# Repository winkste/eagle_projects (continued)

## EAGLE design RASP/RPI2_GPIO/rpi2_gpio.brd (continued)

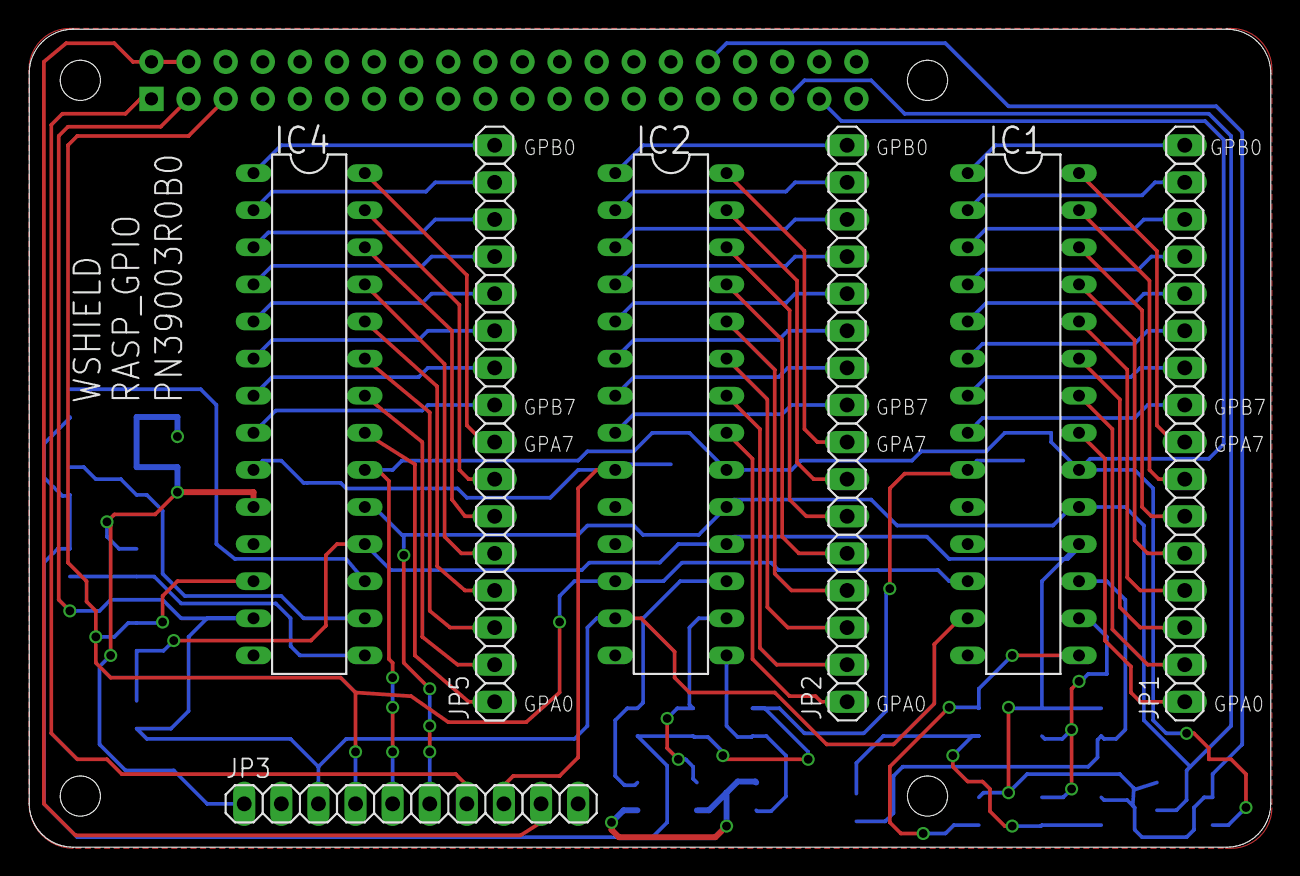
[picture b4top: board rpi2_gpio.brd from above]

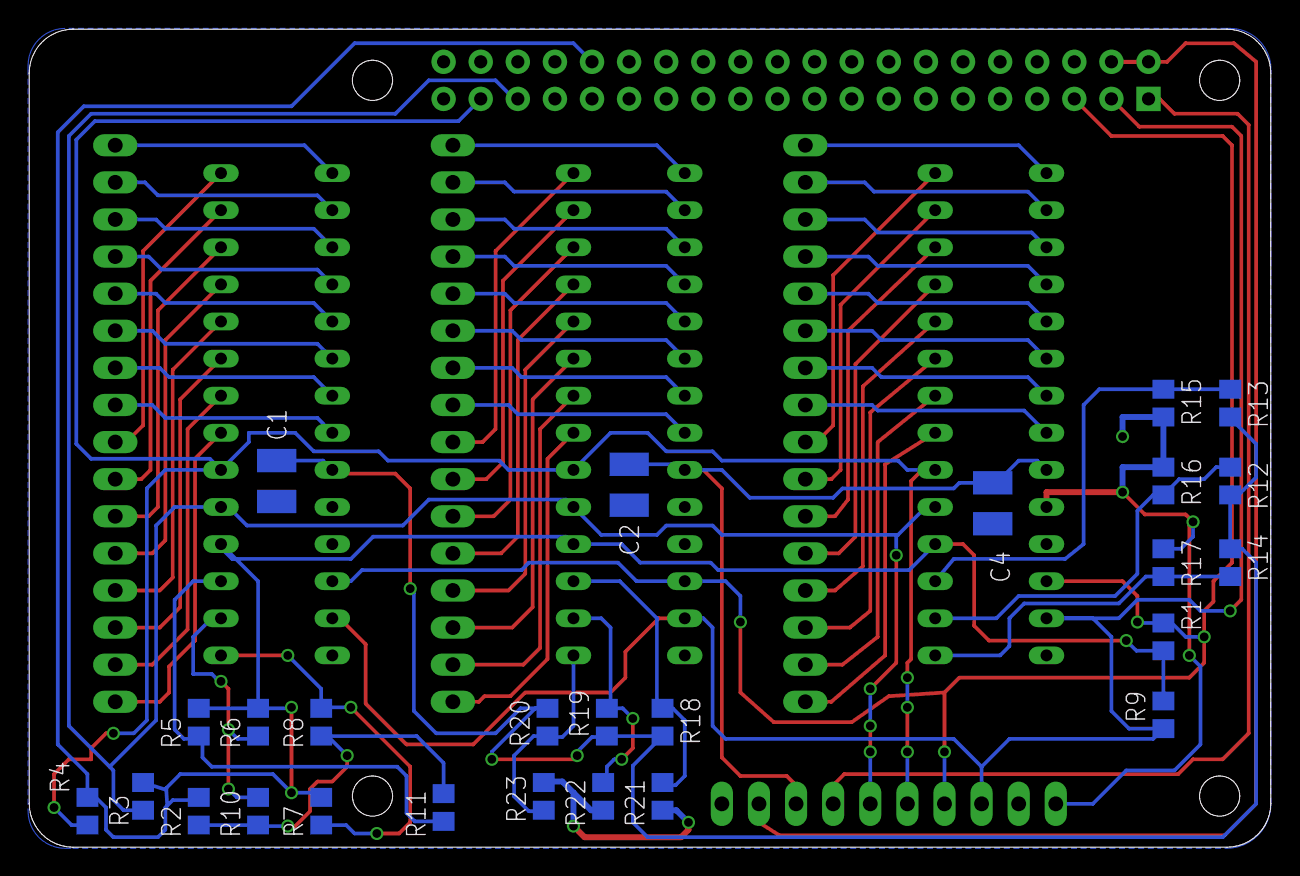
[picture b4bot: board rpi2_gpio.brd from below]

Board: 2 copper layers, 85.0 x 56.0 mm, 34 parts (26 on the bottom side), 67 nets.

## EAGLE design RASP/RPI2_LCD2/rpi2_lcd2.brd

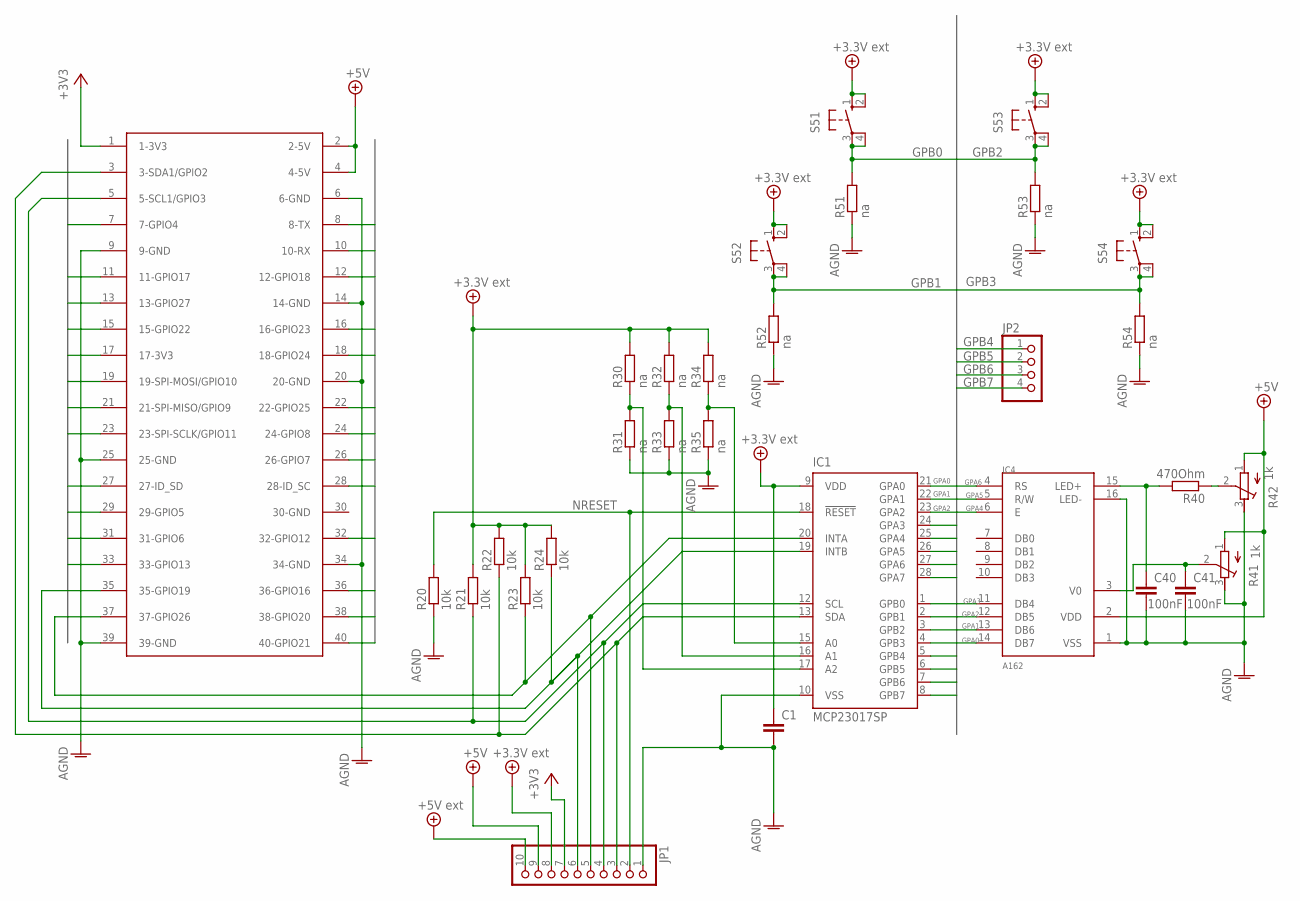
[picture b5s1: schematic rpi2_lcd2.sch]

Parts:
C1: C-EUC1210; C1210
C40, C41: 100nF; C1210
IC1: MCP23017SP; DIL28-3
IC4: A162
JP1: PINHD-1X10; 1X10
JP2: PINHD-1X4; 1X04
R20, R21, R22, R23, R24: 10k; R0805
R30, R31, R32, R33, R34, R35, R51, R52, R53, R54: na; R0805
R40: 470Ohm; R0805
R41, R42: 1k; RTRIM3339P
S51, S52, S53, S54: 10-XX; B3F-10XX
U$1: RASPBERRY-PI+HEADERONLY; RASPBERRY-PI-PLUS-HEADERONLY

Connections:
3.3VEXT: C1.1, IC1.9 (VDD), JP1.8, R21.2, R22.2, R23.2, R24.2, R30.2, R32.2, R34.2, S51.1 (S), S51.2 (S1), S52.1 (S), S52.2 (S1), S53.1 (S), S53.2 (S1), S54.1 (S), S54.2 (S1)
+3V3: JP1.7, U$1.1 (1-3V3)
+5V: IC4.2 (VDD), JP1.9, R41.1 (A), R42.1 (A), U$1.2 (2-5V), U$1.4 (4-5V)
+5V/1: JP1.10
AGND: C1.2, C40.2, C41.2, IC1.10 (VSS), IC4.1 (VSS), IC4.16 (LED-), JP1.1, R20.1, R31.1, R33.1, R35.1, R41.3 (E), R42.3 (E), R51.1, R52.1, R53.1, R54.1, U$1.6 (6-GND), U$1.9 (9-GND), U$1.14 (14-GND), U$1.20 (20-GND), U$1.25 (25-GND), U$1.34 (34-GND), U$1.39 (39-GND)
GPA0: IC1.21 (GPA0), IC4.14 (DB7)
GPA1: IC1.22 (GPA1), IC4.13 (DB6)
GPA2: IC1.23 (GPA2), IC4.12 (DB5)
GPA3: IC1.24 (GPA3), IC4.11 (DB4)
GPA4: IC1.25 (GPA4), IC4.6 (E)
GPA5: IC1.26 (GPA5), IC4.5 (R/W)
GPA6: IC1.27 (GPA6), IC4.4 (RS)
GPA7: IC1.28 (GPA7)
GPB0: IC1.1 (GPB0), R51.2, S51.3, S51.4 (P1)
GPB1: IC1.2 (GPB1), R52.2, S52.3, S52.4 (P1)
GPB2: IC1.3 (GPB2), R53.2, S53.3, S53.4 (P1)
GPB3: IC1.4 (GPB3), R54.2, S54.3, S54.4 (P1)
GPB4: IC1.5 (GPB4), JP2.1
GPB5: IC1.6 (GPB5), JP2.2
GPB6: IC1.7 (GPB6), JP2.3
GPB7: IC1.8 (GPB7), JP2.4
GPIO3: IC1.13 (SDA), JP1.3, R22.1, U$1.3 (3-SDA1/GPIO2)
GPIO5: IC1.12 (SCL), JP1.4, R21.1, U$1.5 (5-SCL1/GPIO3)
GPIO7: U$1.7 (7-GPIO4)
GPIO8: U$1.8 (8-TX)
GPIO10: U$1.10 (10-RX)
GPIO11: U$1.11 (11-GPIO17)
GPIO12: U$1.12 (12-GPIO18)
GPIO13: U$1.13 (13-GPIO27)
GPIO15: U$1.15 (15-GPIO22)
GPIO16: U$1.16 (16-GPIO23)
GPIO17: U$1.17 (17-3V3)
GPIO18: U$1.18 (18-GPIO24)
GPIO19: U$1.19 (19-SPI-MOSI/GPIO10)
GPIO21: U$1.21 (21-SPI-MISO/GPIO9)
GPIO22: U$1.22 (22-GPIO25)
GPIO23: U$1.23 (23-SPI-SCLK/GPIO11)
GPIO24: U$1.24 (24-GPIO8)
GPIO26: U$1.26 (26-GPIO7)
GPIO27: U$1.27 (27-ID_SD)
GPIO28: U$1.28 (28-ID_SC)
GPIO29: U$1.29 (29-GPIO5)
GPIO31: U$1.31 (31-GPIO6)
GPIO32: U$1.32 (32-GPIO12)
GPIO33: U$1.33 (33-GPIO13)
GPIO35: IC1.19 (INTB), JP1.6, R24.1, U$1.35 (35-GPIO19)
GPIO36: U$1.36 (36-GPIO16)
GPIO37: IC1.20 (INTA), JP1.5, R23.1, U$1.37 (37-GPIO26)
GPIO38: U$1.38 (38-GPIO20)
GPIO40: U$1.40 (40-GPIO21)
unnamed: R40.1, R42.2 (S)
unnamed: C40.1, IC4.15 (LED+), R40.2
unnamed: C41.1, IC4.3 (V0), R41.2 (S)
unnamed: IC1.17 (A2), R30.1, R31.2
unnamed: IC1.16 (A1), R32.1, R33.2
unnamed: IC1.15 (A0), R34.1, R35.2
NRESET: IC1.18 (!RESET), JP1.2, R20.2

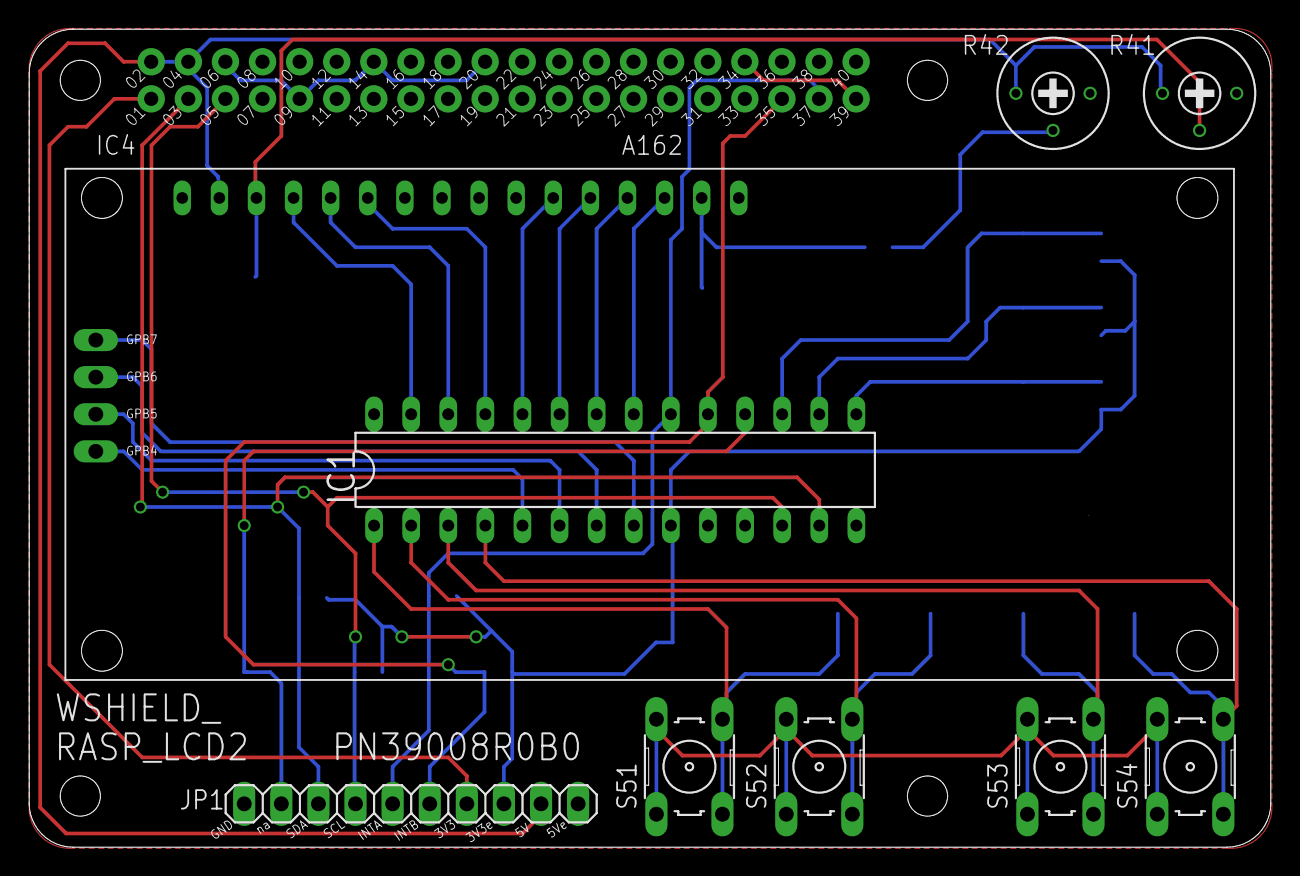
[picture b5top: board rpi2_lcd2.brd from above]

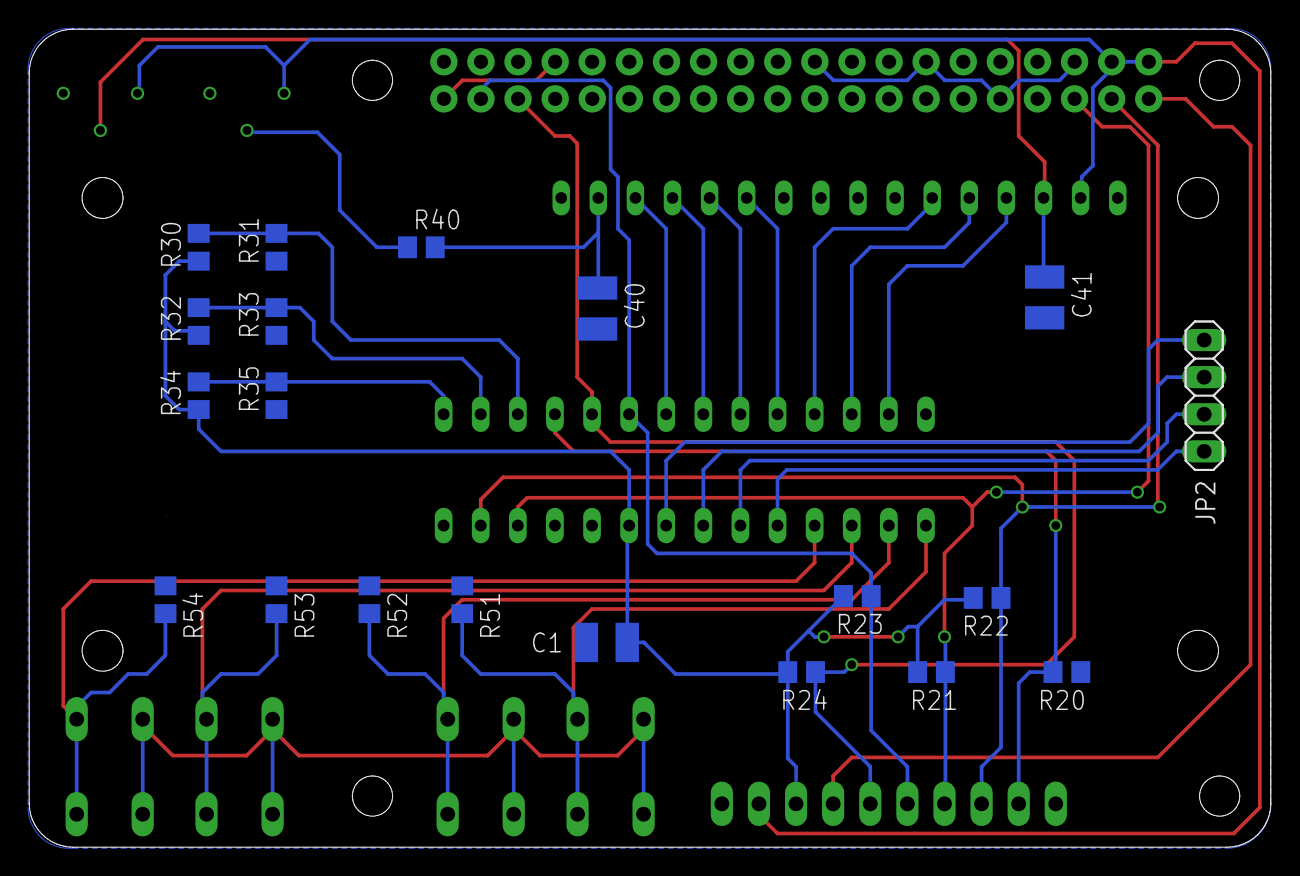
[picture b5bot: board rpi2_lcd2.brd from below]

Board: 2 copper layers, 85.0 x 56.0 mm, 32 parts (21 on the bottom side), 30 nets.

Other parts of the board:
U$2, U$3: BRAND_SWI

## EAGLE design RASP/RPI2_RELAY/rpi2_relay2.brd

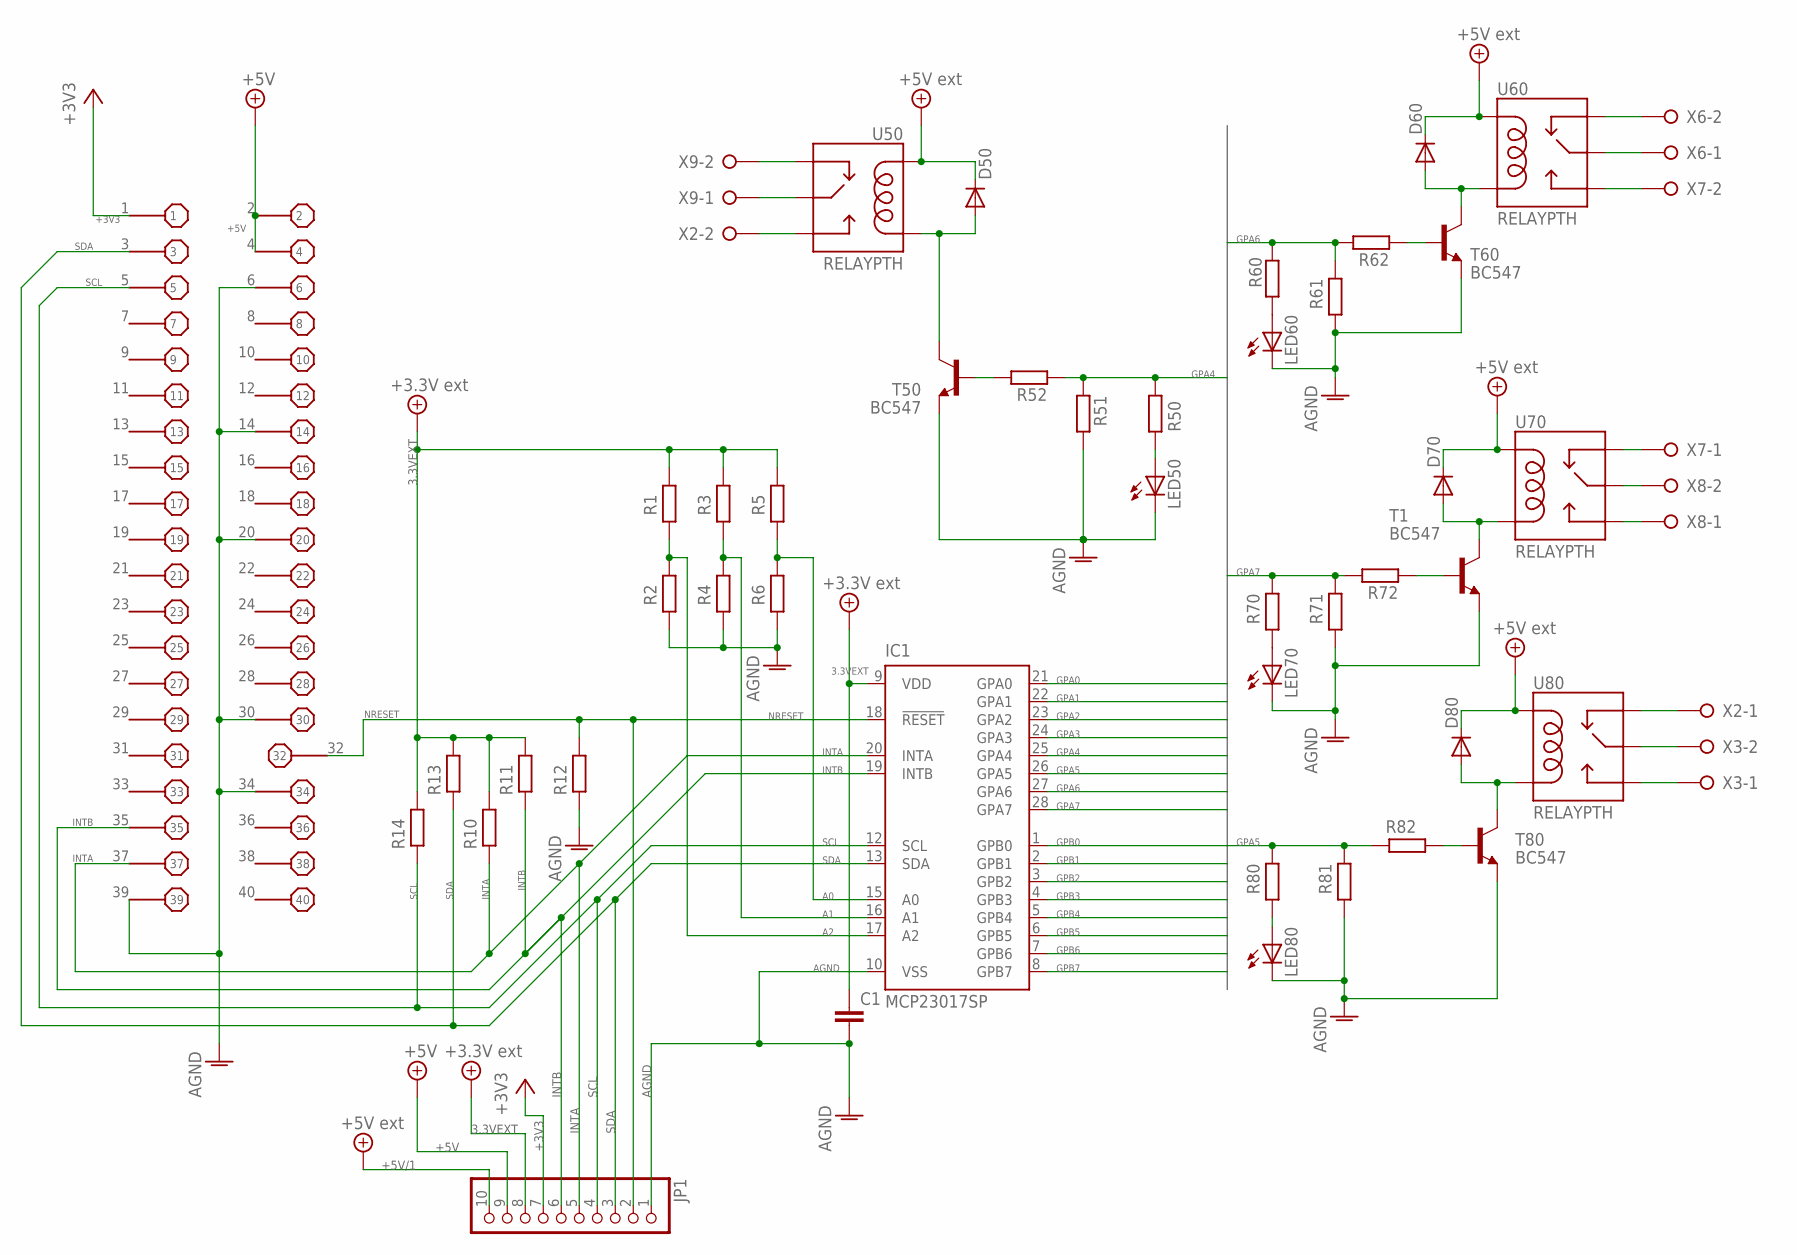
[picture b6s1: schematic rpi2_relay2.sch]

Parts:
C1: C-EUC1210; C1210
D50, D60, D70, D80: 1N4148DO35-7; DO35-7
IC1: MCP23017SP; DIL28-3
JP1: PINHD-1X10; 1X10
LED50, LED60, LED70, LED80: LEDCHIP-LED0805; CHIP-LED0805
R1, R2, R3, R4, R5, R6, R10, R11, R12, R13, R14, R50, R51, R52, R60, R61, R62, R70, R71, R72, R80, R81, R82: R-EU_R0805; R0805
T1, T50, T60, T80: BC547; TO92
U50, U60, U70, U80: RELAYPTH; SRD-05VDC-SL-C
X1: B+_GPIO
X2, X3, X6, X7, X8, X9: W237-02P; W237-132

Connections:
3.3VEXT: C1.1, IC1.9 (VDD), JP1.8, R1.1, R3.1, R5.1, R10.1, R11.1, R13.1, R14.1
+3V3: JP1.7, X1.1
+5V: JP1.9, X1.2, X1.4
+5V/1: D50.C, D60.C, D70.C, D80.C, JP1.10, U50.COIL1, U60.COIL1, U70.COIL1, U80.COIL1
A0: IC1.15 (A0), R5.2, R6.1
A1: IC1.16 (A1), R3.2, R4.1
A2: IC1.17 (A2), R1.2, R2.1
AGND: C1.2, IC1.10 (VSS), JP1.1, LED50.C, LED60.C, LED70.C, LED80.C, R2.2, R4.2, R6.2, R12.2, R51.2, R61.2, R71.2, R81.2, T1.1 (E), T50.1 (E), T60.1 (E), T80.1 (E), X1.6, X1.14, X1.20, X1.30, X1.34, X1.39
GPA0: IC1.21 (GPA0)
GPA1: IC1.22 (GPA1)
GPA2: IC1.23 (GPA2)
GPA3: IC1.24 (GPA3)
GPA4: IC1.25 (GPA4), R50.2, R51.1, R52.1
GPA5: IC1.26 (GPA5), R80.1, R81.1, R82.2
GPA6: IC1.27 (GPA6), R60.2, R61.1, R62.2
GPA7: IC1.28 (GPA7), R70.1, R71.1, R72.2
GPB0: IC1.1 (GPB0)
GPB1: IC1.2 (GPB1)
GPB2: IC1.3 (GPB2)
GPB3: IC1.4 (GPB3)
GPB4: IC1.5 (GPB4)
GPB5: IC1.6 (GPB5)
GPB6: IC1.7 (GPB6)
GPB7: IC1.8 (GPB7)
INTA: IC1.20 (INTA), JP1.5, R10.2, X1.37
INTB: IC1.19 (INTB), JP1.6, R11.2, X1.35
unnamed: LED50.A, R50.1
unnamed: D60.A, T60.3 (C), U60.COIL0
unnamed: LED60.A, R60.1
unnamed: LED70.A, R70.2
unnamed: LED80.A, R80.2
unnamed: R72.1, T1.2 (B)
unnamed: U60.SWCOMMON, X6.1
unnamed: U60.SWCLOSED (SWCLOSE), X6.2
unnamed: U60.SWOPEN, X7.2
unnamed: D70.A, T1.3 (C), U70.COIL0
unnamed: U70.SWCLOSED (SWCLOSE), X7.1
unnamed: U70.SWOPEN, X8.1
unnamed: U70.SWCOMMON, X8.2
unnamed: D80.A, T80.3 (C), U80.COIL0
unnamed: R82.1, T80.2 (B)
unnamed: U80.SWCOMMON, X3.2
unnamed: U80.SWOPEN, X3.1
unnamed: U80.SWCLOSED (SWCLOSE), X2.1
unnamed: D50.A, T50.3 (C), U50.COIL0
unnamed: U50.SWCOMMON, X9.1
unnamed: U50.SWOPEN, X2.2
unnamed: U50.SWCLOSED (SWCLOSE), X9.2
unnamed: R52.2, T50.2 (B)
unnamed: R62.1, T60.2 (B)
NRESET: IC1.18 (!RESET), JP1.2, R12.1, X1.32
SCL: IC1.12 (SCL), JP1.4, R14.2, X1.5
SDA: IC1.13 (SDA), JP1.3, R13.2, X1.3

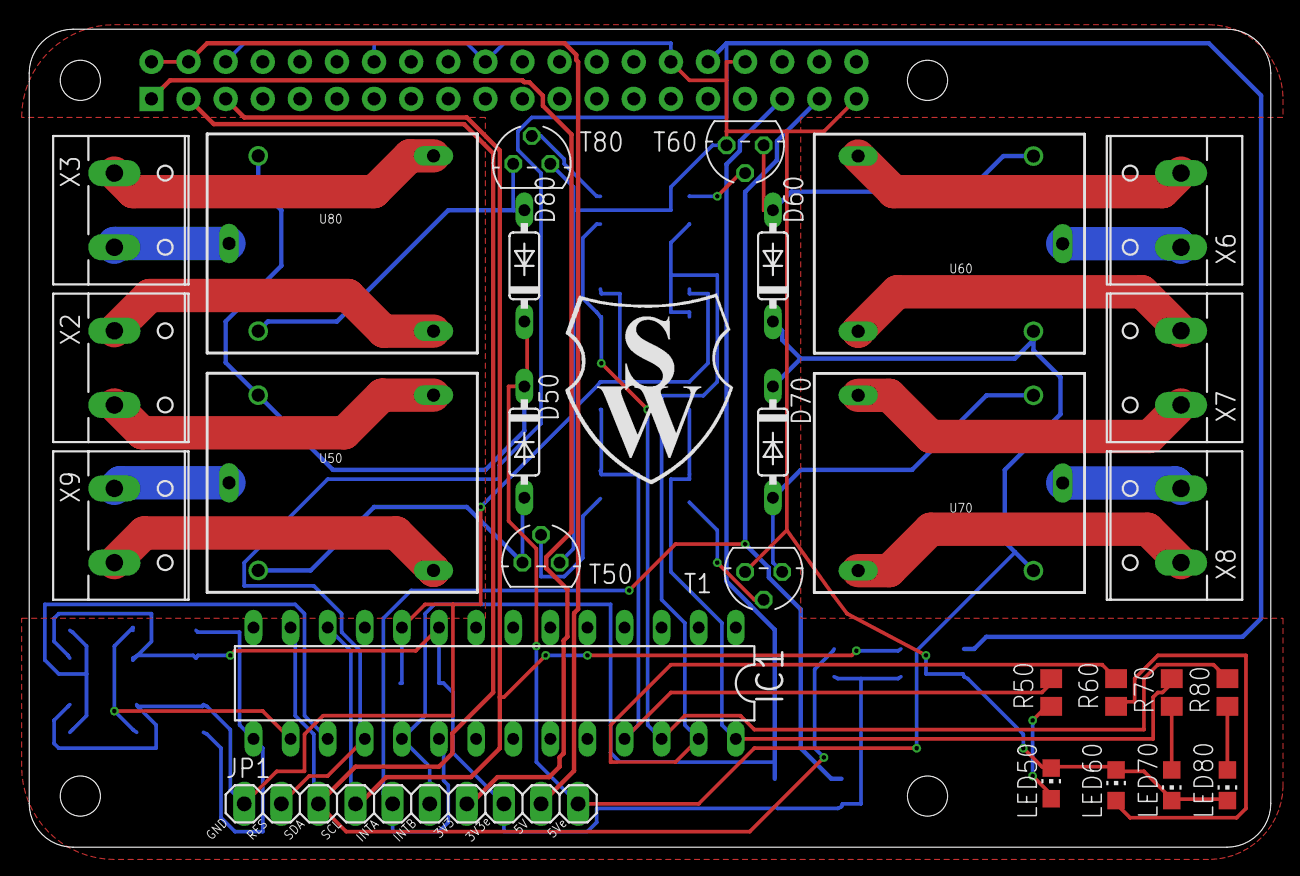
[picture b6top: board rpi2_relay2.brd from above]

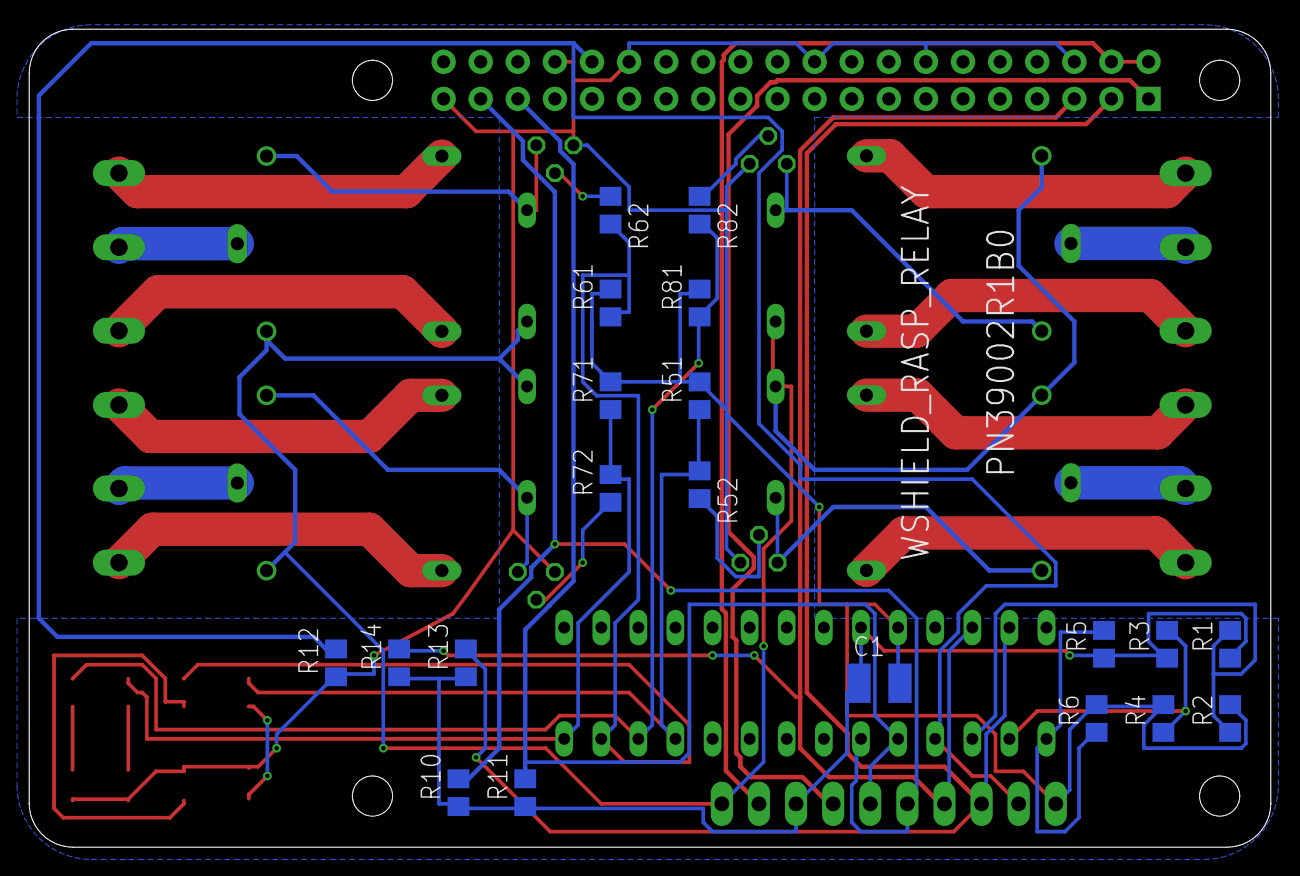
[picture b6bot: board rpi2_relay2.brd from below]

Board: 2 copper layers, 85.0 x 56.0 mm, 50 parts (20 on the bottom side), 41 nets.

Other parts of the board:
U$1: BRAND_SWI_10X14
